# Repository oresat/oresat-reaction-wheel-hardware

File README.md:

# DO NOT TRY TO MAKE THIS

## License

This source describes Open Hardware and is licensed under the CERN-OHL-S v2.
You may redistribute and modify it under the terms of the
[CERN-OHL-S v2](https://ohwr.org/cern_ohl_s_v2.txt); the full text is in
[LICENSE](LICENSE).

This source is distributed WITHOUT ANY EXPRESS OR IMPLIED WARRANTY, INCLUDING
OF MERCHANTABILITY, SATISFACTORY QUALITY AND FITNESS FOR A PARTICULAR PURPOSE.
Please see the CERN-OHL-S v2 for applicable conditions.

Source location: https://gitlab.com/solomondg/oresat-rw-board-rev8

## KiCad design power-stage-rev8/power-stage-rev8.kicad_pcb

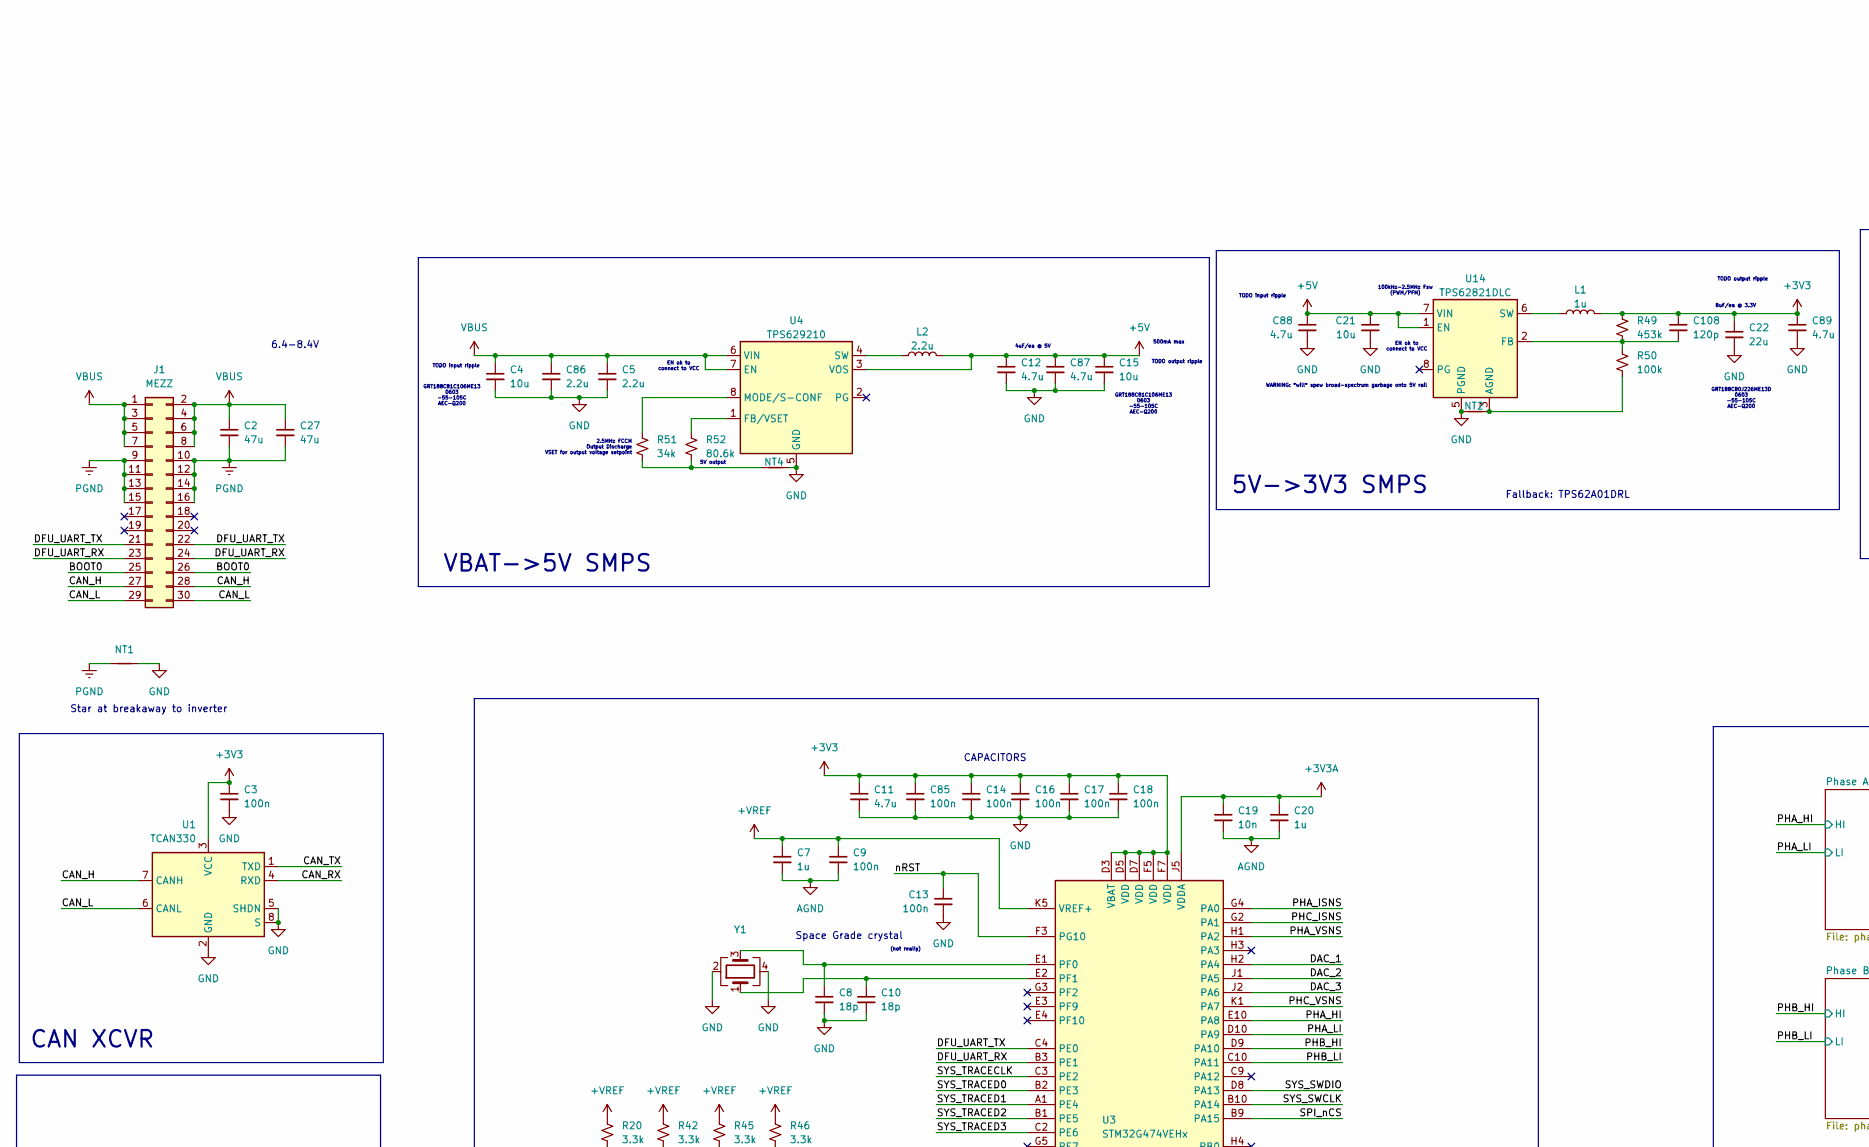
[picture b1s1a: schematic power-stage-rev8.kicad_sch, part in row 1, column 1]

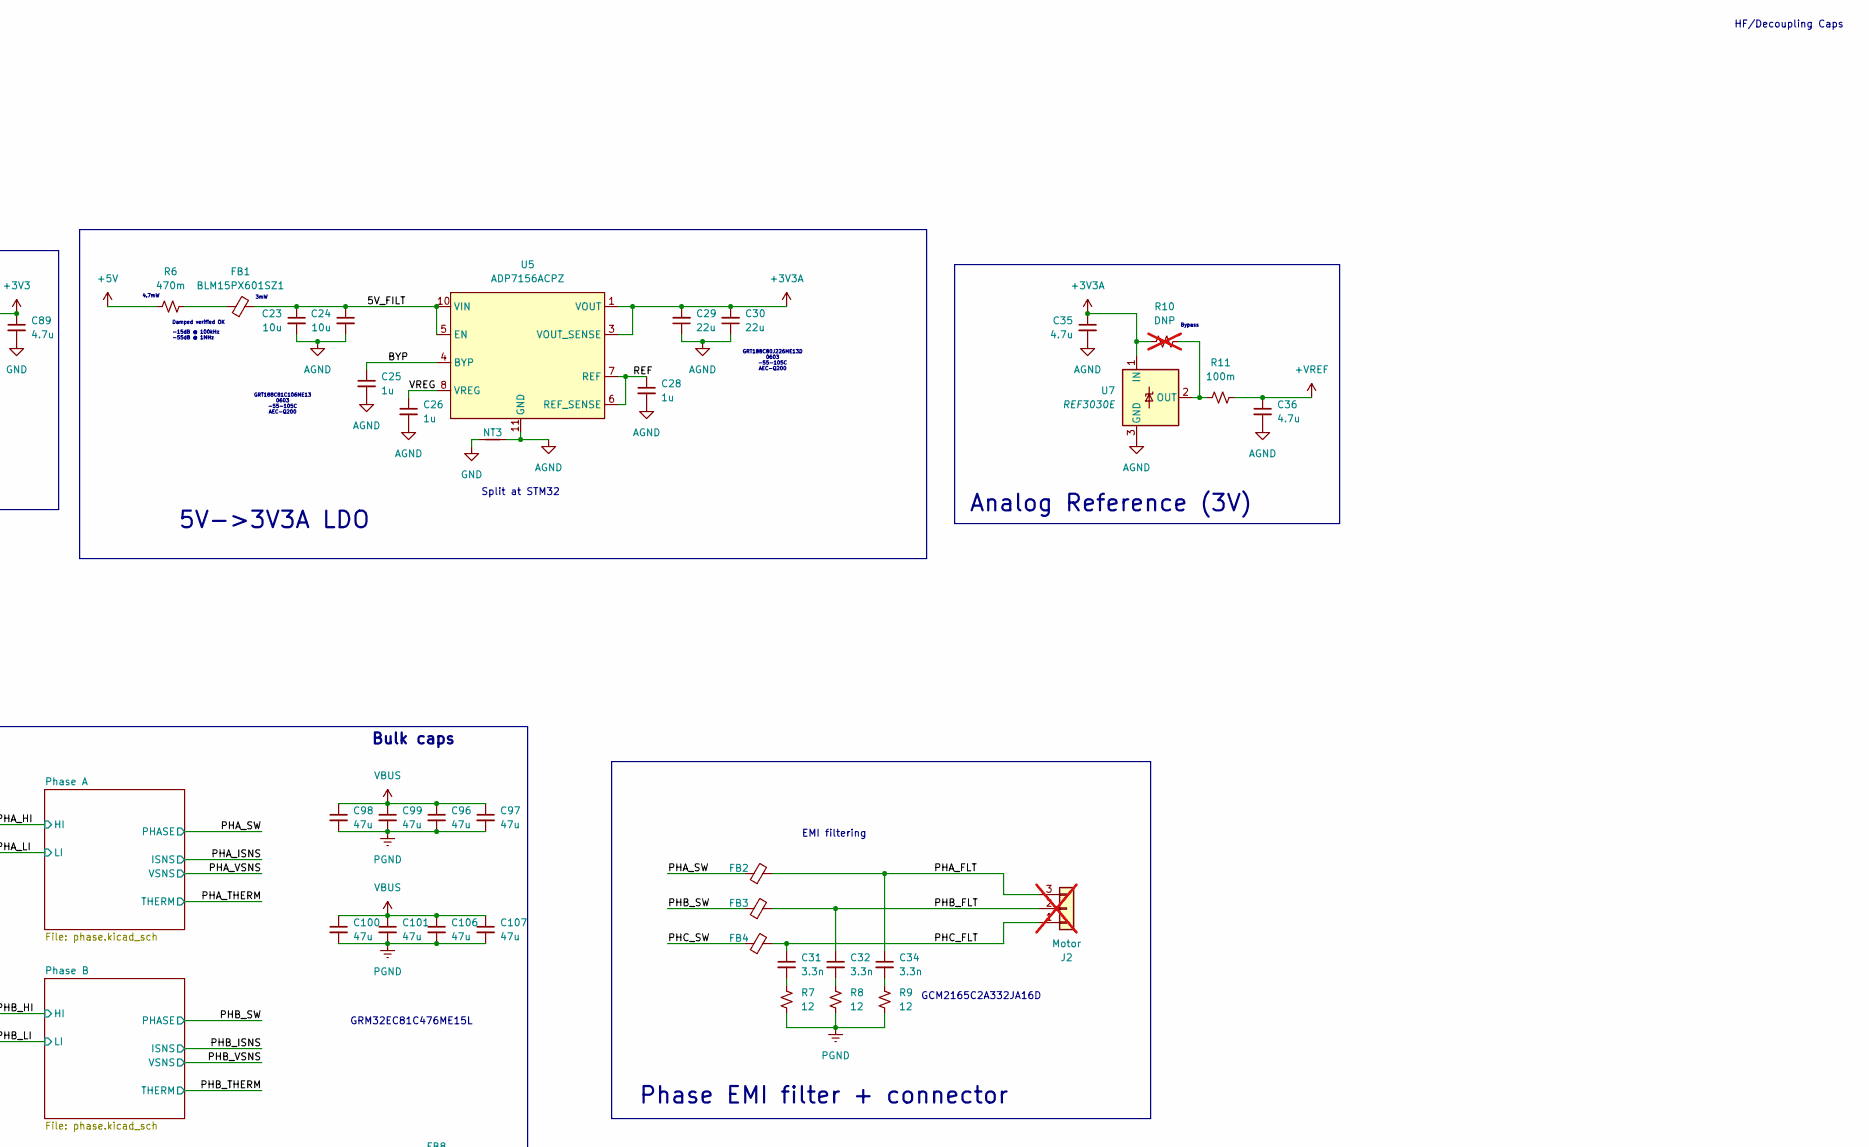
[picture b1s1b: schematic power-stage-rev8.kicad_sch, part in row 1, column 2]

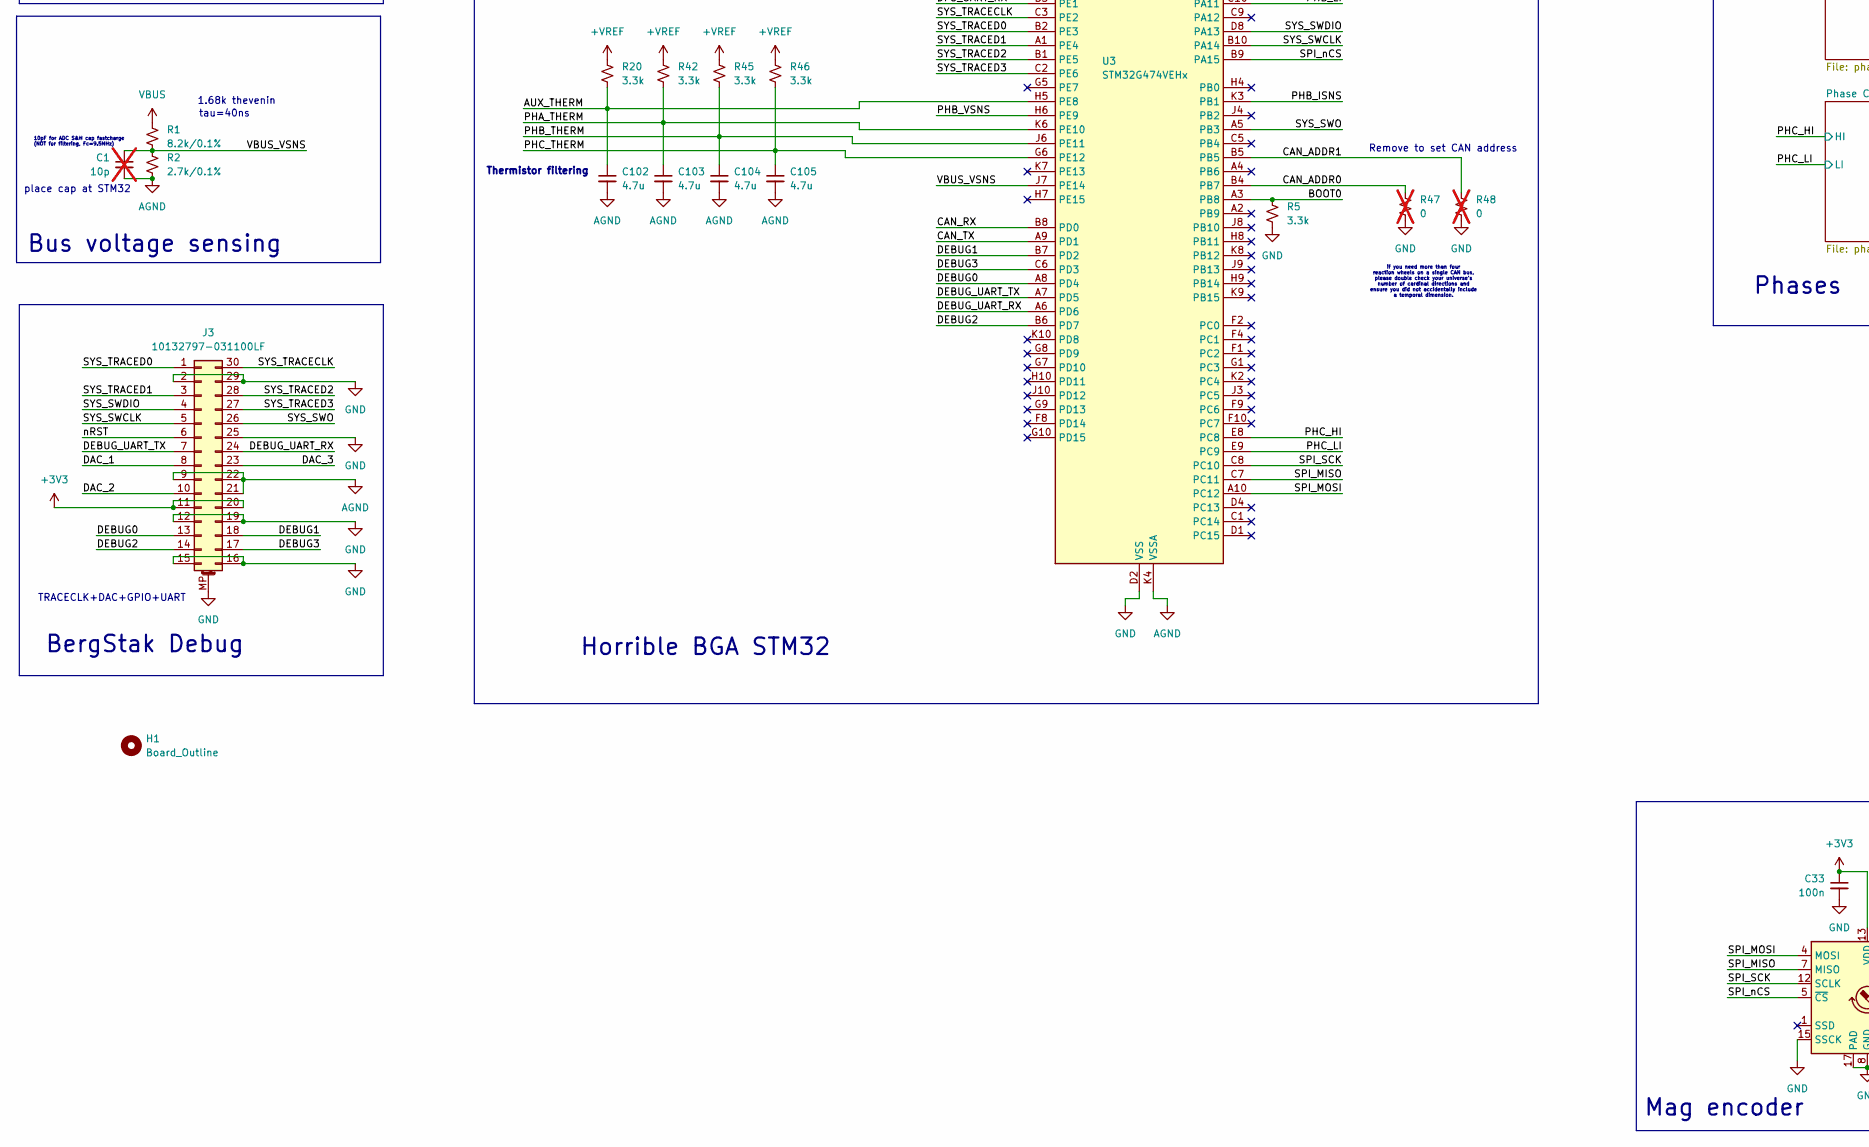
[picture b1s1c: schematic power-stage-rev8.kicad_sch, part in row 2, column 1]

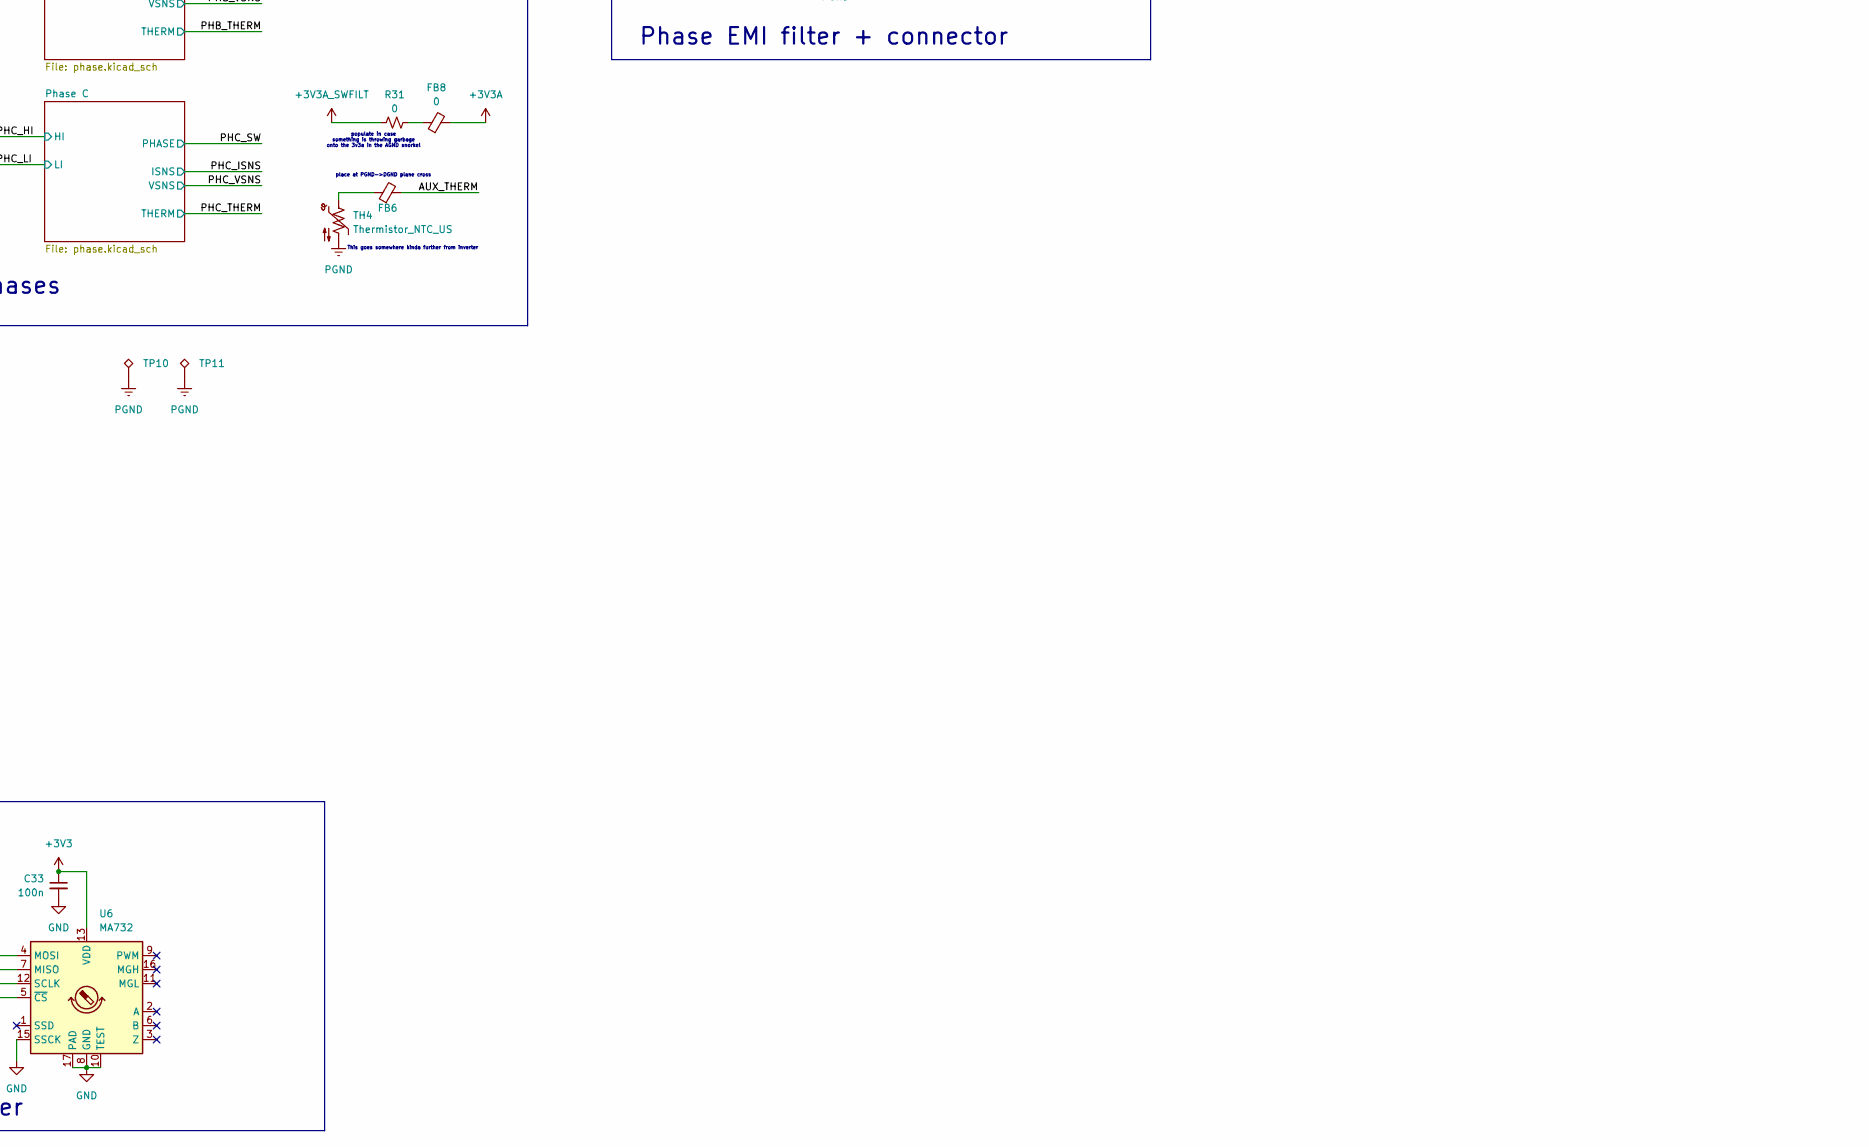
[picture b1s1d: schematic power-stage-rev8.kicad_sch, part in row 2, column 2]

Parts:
C1: 10p; C_0402_1005Metric; MPN GCM1555C1H100FA16D; not fitted
C2, C27, C96, C97, C98, C99, C100, C101, C106, C107: 47u; C_1210_3225Metric; MPN GRT32EC81C476KE13L
C3, C9, C13, C14, C16, C17, C18, C33, C85: 100n; C_0402_1005Metric; MPN GRT155R71E104KE01J
C4, C15, C21, C23, C24: 10u; C_0603_1608Metric; MPN GRT188C81C106ME13D
C5, C86: 2.2u; C_0402_1005Metric; MPN GRT155C81C225ME13D
C7, C20, C25, C26, C28: 1u; C_0402_1005Metric; MPN GRT155C81A105ME01D
C8, C10: 18p; C_0402_1005Metric; MPN GCM1555C1H180JA16D
C11, C12, C35, C36, C87, C88, C89, C102, C103, C104, C105: 4.7u; C_0402_1005Metric; MPN GRT155C81A475ME13J
C19: 10n; C_0402_1005Metric; MPN GCM155R71H103KA55D
C22, C29, C30: 22u; C_0603_1608Metric; MPN GRT188C80J226ME13D
C31, C32, C34: 3.3n; C_0805_2012Metric; MPN GCM2165C2A332JA16D
C108: 120p; C_0402_1005Metric; MPN GRM1555C1H121JA01D
FB1, FB6: BLM15PX601SZ1; L_0402_1005Metric; MPN BLM15PX601SZ1D
FB2, FB3, FB4: BLM31SN500SN1L; L_1206_3216Metric; MPN BLM31SN500SN1L
FB8: 0; L_0402_1005Metric; MPN AC0402FR-070RL
H1: Board_Outline; board_def_rev8.0
J1: MEZZ; 0555600307; MPN 0555600307
J2: Motor; Molex_Micro-Fit_3.0_43650-0315_1x03_P3.00mm_Vertical; not fitted
J3: 10132797-031100LF; 10132797-031100LF_1; MPN 10132797-031100LF
L1: 1u; L_Murata_DFE201612E_2016Metric; MPN DFE201612E-1R0M=P2
L2: 2.2u; L_Murata_DFE201612E_2016Metric; MPN DFE201612E-2R2M=P2
NT1: NetTie_2; NetTie-2_SMD_Pad2.0mm
NT2, NT3, NT4: NetTie_2; NetTie-2_SMD_Pad0.5mm
R1: 8.2k/0.1%; R_0402_1005Metric; MPN RP0402BRD078K2L
R2: 2.7k/0.1%; R_0402_1005Metric; MPN RP0402BRD072K7L
R5, R20, R42, R45, R46: 3.3k; R_0402_1005Metric; MPN AC0402FR-073K3L
R6: 470m; R_0402_1005Metric; MPN PE0402FRF7W0R47L
R7, R8, R9: 12; R_0805_2012Metric; MPN SR0805FR-7T12RL
R10: DNP; R_0402_1005Metric; not fitted
R11: 100m; R_0402_1005Metric; MPN PE0402FRF470R1L
R31: 0; R_0402_1005Metric; MPN AC0402FR-070RL
R47, R48: 0; R_0402_1005Metric; MPN AC0402FR-070RL; not fitted
R49: 453k; R_0402_1005Metric; MPN AC0402FR-07453KL
R50: 100k; R_0402_1005Metric; MPN AC0402FR-07100KL
R51: 34k; R_0402_1005Metric; MPN AC0402FR-0734KL
R52: 80.6k; R_0402_1005Metric; MPN AC0402FR-0780K6L
TH4: Thermistor_NTC_US; R_0402_1005Metric; MPN NCU15XH103F6SRC
TP10, TP11: TestPoint_Alt; TestPoint_Pad_1.0x1.0mm_NoSilk
U1: TCAN330; SOT-23-8; MPN TCAN330DCNR
U3: STM32G474VEHx; TFBGA-100_8x8mm_Layout10x10_P0.8mm; MPN STM32G474VEH3
U4: TPS629210; SOT-583-8; MPN TPS629210DRLR
U5: ADP7156ACPZ; DFN-10-1EP_3x3mm_P0.5mm_EP1.65x2.38mm; MPN ADP7156ACPZ-3.3-R7
U6: MA732; QFN-16-1EP_3x3mm_P0.5mm_EP1.75x1.75mm; MPN MA732GQ-Z
U7: REF3030E; SOT-23; MPN REF3030AIDBZR
U14: TPS62821DLC; Texas_VSON-HR-8_1.5x2mm_P0.5mm; MPN TPS62821DLCR
Y1: Crystal_GND24; Crystal_SMD_2016-4Pin_2.0x1.6mm; MPN LFXTAL071255

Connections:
+3V3: C3.1, C11.1, C14.1, C16.1, C17.1, C18.1, C22.1, C33.1, C85.1, C89.1, C108.1, J3.11, J3.20, L1.2, R49.1, U1.3 (VCC), U3.D3 (VBAT), U3.D5 (VDD), U3.D7 (VDD), U3.F5 (VDD), U3.F7 (VDD), U6.13 (VDD)
+3V3A: C19.1, C20.1, C29.2, C30.2, C35.1, FB8.2, R10.1, U3.J5 (VDDA), U5.1 (VOUT), U5.2 (VOUT), U5.3 (VOUT_SENSE), U7.1 (IN)
+3V3A_SWFILT: R31.1; also elsewhere on the board
+5V: C12.1, C15.1, C21.1, C87.1, C88.1, L2.2, R6.1, U4.3 (VOS), U14.1 (EN), U14.7 (VIN); also elsewhere on the board
+VREF: C7.1, C9.1, C36.1, R11.2, R20.1, R42.1, R45.1, R46.1, U3.K5 (VREF+); also elsewhere on the board
/5V_FILT: C23.1, C24.1, FB1.2, U5.5 (EN), U5.9 (VIN), U5.10 (VIN)
/AUX_THERM: C102.1, FB6.2, R20.2, U3.H5 (PE8)
/BOOT0: J1.25, J1.26, R5.1, U3.A3 (PB8)
/BYP: C25.1, U5.4 (BYP)
/CAN_ADDR0: R47.1, U3.B4 (PB7)
/CAN_ADDR1: R48.1, U3.B5
/CAN_H: J1.27, J1.28, U1.7 (CANH)
/CAN_L: J1.29, J1.30, U1.6 (CANL)
/CAN_RX: U1.4 (RXD), U3.B8 (PD0)
/CAN_TX: U1.1 (TXD), U3.A9 (PD1)
/DAC_1: J3.8, U3.H2 (PA4)
/DAC_2: J3.10, U3.J1 (PA5)
/DAC_3: J3.23, U3.J2 (PA6)
/DEBUG0: J3.13, U3.A8 (PD4)
/DEBUG1: J3.18, U3.B7 (PD2)
/DEBUG2: J3.14, U3.B6 (PD7)
/DEBUG3: J3.17, U3.C6 (PD3)
/DEBUG_UART_RX: J3.24, U3.A6 (PD6)
/DEBUG_UART_TX: J3.7, U3.A7 (PD5)
/DFU_UART_RX: J1.23, J1.24, U3.B3 (PE1)
/DFU_UART_TX: J1.21, J1.22, U3.C4 (PE0)
/PHA_FLT: C34.1, FB2.2, J2.3
/PHA_HI: U3.E10 (PA8); also elsewhere on the board
/PHA_ISNS: U3.G4 (PA0); also elsewhere on the board
/PHA_LI: U3.D10 (PA9); also elsewhere on the board
/PHA_SW: FB2.1; also elsewhere on the board
/PHA_THERM: C103.1, R42.2, U3.K6 (PE10); also elsewhere on the board
/PHA_VSNS: U3.H1 (PA2); also elsewhere on the board
/PHB_FLT: C32.1, FB3.2, J2.2
/PHB_HI: U3.D9 (PA10); also elsewhere on the board
/PHB_ISNS: U3.K3 (PB1); also elsewhere on the board
/PHB_LI: U3.C10 (PA11); also elsewhere on the board
/PHB_SW: FB3.1; also elsewhere on the board
/PHB_THERM: C104.1, R45.2, U3.J6 (PE11); also elsewhere on the board
/PHB_VSNS: U3.H6 (PE9); also elsewhere on the board
/PHC_FLT: C31.1, FB4.2, J2.1
/PHC_HI: U3.E8 (PC8); also elsewhere on the board
/PHC_ISNS: U3.G2 (PA1); also elsewhere on the board
/PHC_LI: U3.E9 (PC9); also elsewhere on the board
/PHC_SW: FB4.1; also elsewhere on the board
/PHC_THERM: C105.1, R46.2, U3.G6 (PE12); also elsewhere on the board
/PHC_VSNS: U3.K1 (PA7); also elsewhere on the board
/REF: C28.1, U5.6 (REF_SENSE), U5.7 (REF)
/SPI_MISO: U3.C7 (PC11), U6.7 (MISO)
/SPI_MOSI: U3.A10 (PC12), U6.4 (MOSI)
/SPI_SCK: U3.C8 (PC10), U6.12 (SCLK)
/SPI_nCS: U3.B9 (PA15), U6.5 (~CS)
/SYS_SWCLK: J3.5, U3.B10 (PA14)
/SYS_SWDIO: J3.4, U3.D8 (PA13)
/SYS_SWO: J3.26, U3.A5 (PB3)
/SYS_TRACECLK: J3.30, U3.C3 (PE2)
/SYS_TRACED0: J3.1, U3.B2 (PE3)
/SYS_TRACED1: J3.3, U3.A1 (PE4)
/SYS_TRACED2: J3.28, U3.B1 (PE5)
/SYS_TRACED3: J3.27, U3.C2 (PE6)
/VBUS_VSNS: C1.1, R1.2, R2.1, U3.J7 (PE14)
/VREG: C26.1, U5.8 (VREG)
/nRST: C13.1, J3.6, U3.F3 (PG10)
AGND: C1.2, C7.2, C9.2, C19.2, C20.2, C23.2, C24.2, C25.2, C26.2, C28.2, C29.1, C30.1, C35.2, C36.2, C102.2, C103.2, C104.2, C105.2, J3.9, J3.21, J3.22, NT3.2, R2.2, U3.K4 (VSSA), U5.11 (GND), U7.3 (GND); also elsewhere on the board
GND: C3.2, C4.2, C5.2, C8.2, C10.2, C11.2, C12.2, C13.2, C14.2, C15.2, C16.2, C17.2, C18.2, C21.2, C22.2, C33.2, C85.2, C86.2, C87.2, C88.2, C89.2, J3.2, J3.12, J3.15, J3.16, J3.19, J3.25, J3.29, J3.MP (MountPin), NT1.2, NT2.1, NT3.1, NT4.2, R5.2, R47.2, R48.2, U1.2 (GND), U1.5 (SHDN), U1.8 (S), U3.D2 (VSS), U3.D6 (VSS), U3.E5 (VSS), U3.E6 (VSS), U3.E7 (VSS), U3.F6 (VSS), U4.5 (GND), U6.8 (GND), U6.10 (TEST), U6.15 (SSCK), U6.17 (PAD), U14.5 (PGND), Y1.2, Y1.4; also elsewhere on the board
unnamed: C31.2, R7.1
unnamed: C32.2, R8.1
unnamed: C34.2, R9.1
unnamed: FB1.1, R6.2
unnamed: FB6.1, TH4.1
unnamed: FB8.1, R31.2
unnamed: NT4.1, R51.2, R52.2
unnamed: C8.1, U3.E1 (PF0), Y1.3
unnamed: C10.1, U3.E2 (PF1), Y1.1
unnamed: R52.1, U4.1 (FB/VSET)
unnamed: R51.1, U4.8 (MODE/S-CONF)
unnamed: L2.1, U4.4 (SW)
unnamed: R10.2, R11.1, U7.2 (OUT)
unnamed: NT2.2, R50.2, U14.3 (AGND)
unnamed: C108.2, R49.2, R50.1, U14.2 (FB)
unnamed: L1.1, U14.6 (SW)
PGND: C2.2, C27.2, C96.2, C97.2, C98.2, C99.2, C100.2, C101.2, C106.2, C107.2, J1.9, J1.10, J1.11, J1.12, J1.13, J1.14, J1.15, J1.16, NT1.1, R7.2, R8.2, R9.2, TH4.2, TP10.1 (1_1), TP11.1 (1_1); also elsewhere on the board
VBUS: C2.1, C4.1, C5.1, C27.1, C86.1, C96.1, C97.1, C98.1, C99.1, C100.1, C101.1, C106.1, C107.1, J1.1, J1.2, J1.3, J1.4, J1.5, J1.6, J1.7, J1.8, R1.1, U4.6 (VIN), U4.7 (EN); also elsewhere on the board

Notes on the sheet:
Horrible BGA STM32
4.7mW
8uF/ea @ 3.3V
TRACECLK+DAC+GPIO+UART
GRT188C81C106ME13 0603 -55-105C AEC-Q200
Bypass
-15dB @ 100kHz -55dB @ 1MHz
populate in case something is throwing garbage onto the 3v3a in the AGND snorkel
Space Grade crystal
place at PGND->DGND plane cross
3mW
Bulk caps
GRT188C80J226ME13D 0603 -55-105C AEC-Q200
tau=40ns
VBAT->5V SMPS
2.5MHz FCCM Output Discharge VSET for output voltage setpoint
500mA max
(not really)
10pF for ADC S&H cap fastcharge (NOT for filtering, Fc=9.5MHz)
CAN XCVR
EN ok to connect to VCC
CAPACITORS
TODO output ripple
Remove to set CAN address
Bus voltage sensing
TODO input ripple
This goes somewhere kinda further from inverter
HF/Decoupling Caps
Mag encoder
1.68k thevenin
Star at breakaway to inverter
EMI filtering
if you need more than four reaction wheels on a single CAN bus, please double check your universe's number of cardinal directions and ensure you did not accidentally include a temporal dimension.
place cap at STM32
Split at STM32
100kHz-2.5MHz Fsw (PWM/PFM)
GRM32EC81C476ME15L
Damped verified OK
4uF/ea @ 5V
Phases

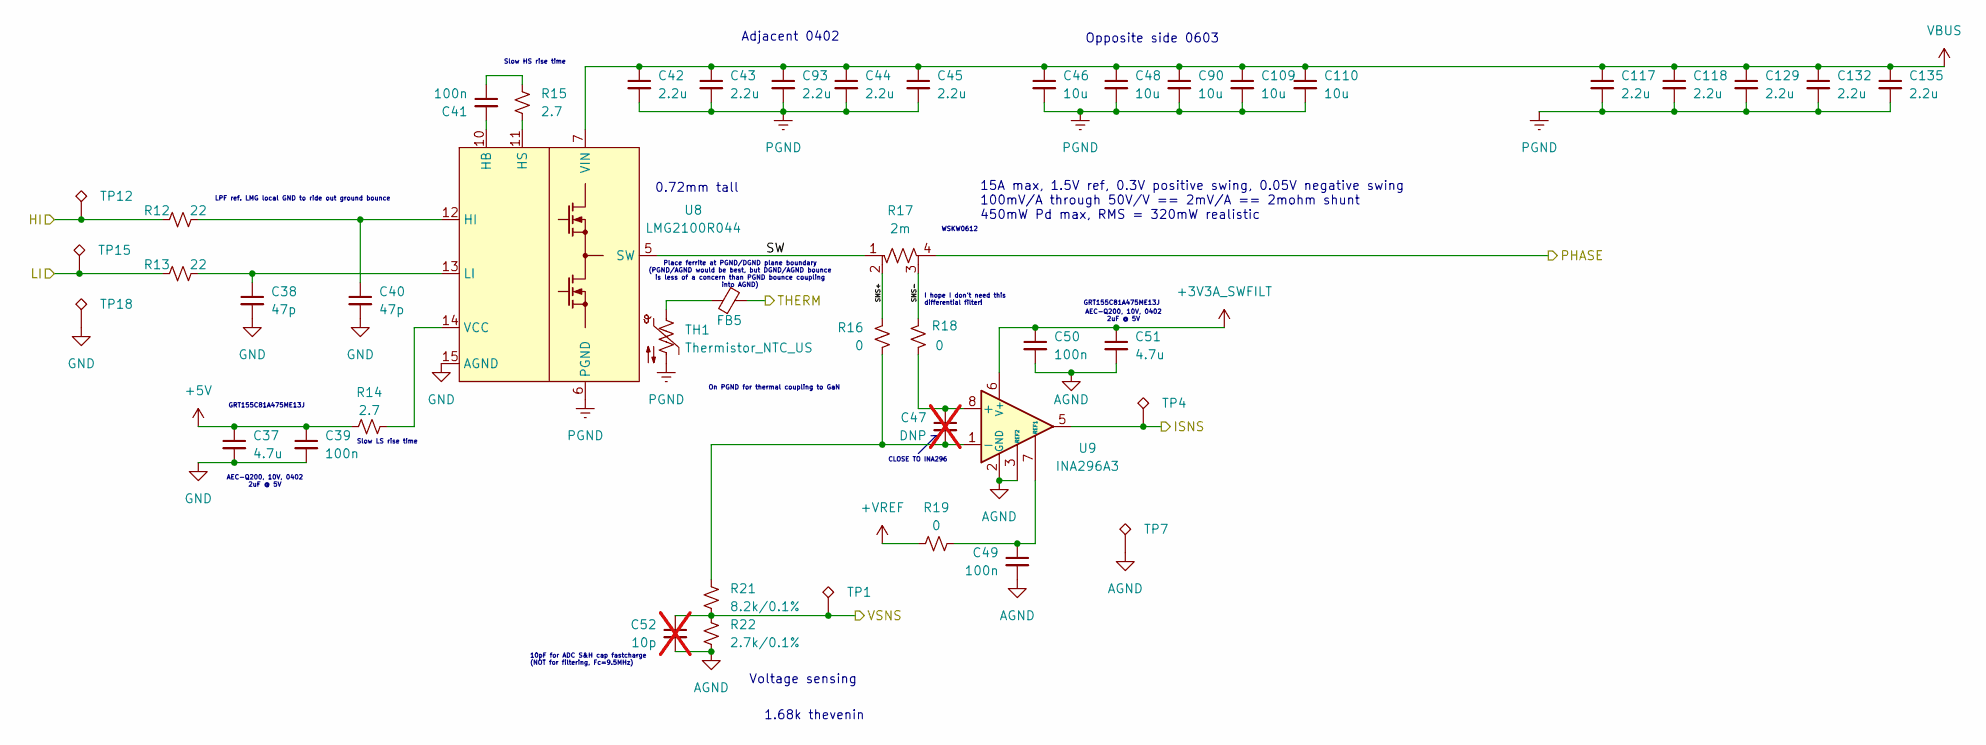
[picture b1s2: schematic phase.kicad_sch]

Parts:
C37, C51: 4.7u; C_0402_1005Metric; MPN GRT155C81A475ME13J
C38, C40: 47p; C_0402_1005Metric; MPN GCM1555C1H470JA16D
C39, C41, C49, C50: 100n; C_0402_1005Metric; MPN GRT155R71E104KE01J
C42, C43, C44, C45, C93, C117, C118, C129, C132, C135: 2.2u; C_0402_1005Metric; MPN GRT155C81C225ME13D
C46, C48, C90, C109, C110: 10u; C_0603_1608Metric; MPN GRT188C81C106ME13D
C47: DNP; C_0402_1005Metric; not fitted
C52: 10p; C_0402_1005Metric; MPN GCM1555C1H100FA16D; not fitted
FB5: BLM15PX601SZ1; L_0402_1005Metric; MPN BLM15PX601SZ1D
R12, R13: 22; R_0402_1005Metric; MPN AC0402FR-0722RL
R14, R15: 2.7; R_0402_1005Metric; MPN AC0402FR-072R7L
R16, R18, R19: 0; R_0402_1005Metric; MPN AC0402FR-070RL
R17: 2m; R_Shunt_Vishay_WSKW0612; MPN WSKW06122L000FEA
R21: 8.2k/0.1%; R_0402_1005Metric; MPN RP0402BRD078K2L
R22: 2.7k/0.1%; R_0402_1005Metric; MPN RP0402BRD072K7L
TH1: Thermistor_NTC_US; R_0402_1005Metric; MPN NCU15XH103F6SRC
TP1, TP4, TP7, TP12, TP15, TP18: TestPoint_Alt; TestPoint_Pad_1.0x1.0mm_NoSilk
U8: LMG2100R044; TI_torment_nexus; MPN LMG2100R044RARR
U9: INA296A3; SOT-23-8; MPN INA296A3QDDFRQ1

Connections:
+3V3A_SWFILT: C50.1, C51.1, U9.6 (V+); also elsewhere on the board
+5V: C37.1, C39.1, R14.1; also elsewhere on the board
+VREF: R19.1; also elsewhere on the board
/PHA_HI: R12.2, TP12.1 (1_1); also elsewhere on the board
/PHA_ISNS: TP4.1 (1_1), U9.5; also elsewhere on the board
/PHA_LI: R13.1, TP15.1 (1_1); also elsewhere on the board
/PHA_SW: R17.4; also elsewhere on the board
/PHA_THERM: FB5.2; also elsewhere on the board
/PHA_VSNS: C52.1, R21.2, R22.1, TP1.1 (1_1); also elsewhere on the board
/Phase A/SNS+: R16.1, R17.2
/Phase A/SNS-: R17.3, R18.2
/Phase A/SW: R17.1, U8.5 (SW)
AGND: C49.2, C50.2, C51.2, C52.2, R22.2, TP7.1 (1_1), U9.2 (GND), U9.3 (REF2), U9.4 (GND); also elsewhere on the board
GND: C37.2, C38.2, C39.2, C40.2, TP18.1 (1_1), U8.15 (AGND); also elsewhere on the board
unnamed: C41.1, R15.1
unnamed: FB5.1, TH1.1
unnamed: C41.2, U8.10 (HB)
unnamed: C40.1, R12.1, U8.12 (HI)
unnamed: R15.2, U8.11 (HS)
unnamed: C38.1, R13.2, U8.13 (LI)
unnamed: R14.2, U8.14 (VCC)
unnamed: C47.1, R18.1, U9.8 (+)
unnamed: C47.2, R16.2, R21.1, U9.1 (-)
unnamed: C49.1, R19.2, U9.7 (REF1)
PGND: C42.2, C43.2, C44.2, C45.2, C46.2, C48.2, C90.2, C93.2, C109.2, C110.2, C117.2, C118.2, C129.2, C132.2, C135.2, TH1.2, U8.6 (PGND), U8.17 (PGND); also elsewhere on the board
VBUS: C42.1, C43.1, C44.1, C45.1, C46.1, C48.1, C90.1, C93.1, C109.1, C110.1, C117.1, C118.1, C129.1, C132.1, C135.1, U8.7 (VIN); also elsewhere on the board

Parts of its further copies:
C53, C67, C69, C83: 4.7u; C_0402_1005Metric; MPN GRT155C81A475ME13J
C54, C56, C70, C72: 47p; C_0402_1005Metric; MPN GCM1555C1H470JA16D
C55, C57, C65, C66, C71, C73, C81, C82: 100n; C_0402_1005Metric; MPN GRT155R71E104KE01J
C58, C59, C60, C61, C74, C75, C76, C77, C94, C95, C122, C123, C127, C128, C130, C131, C133, C134, C136, C137: 2.2u; C_0402_1005Metric; MPN GRT155C81C225ME13D
C62, C64, C78, C80, C91, C92, C112, C113, C115, C116: 10u; C_0603_1608Metric; MPN GRT188C81C106ME13D
C63, C79: DNP; C_0402_1005Metric; not fitted
C68, C84: 10p; C_0402_1005Metric; MPN GCM1555C1H100FA16D; not fitted
FB7, FB9: BLM15PX601SZ1; L_0402_1005Metric; MPN BLM15PX601SZ1D
R23, R24, R34, R35: 22; R_0402_1005Metric; MPN AC0402FR-0722RL
R25, R26, R36, R37: 2.7; R_0402_1005Metric; MPN AC0402FR-072R7L
R27, R29, R30, R38, R40, R41: 0; R_0402_1005Metric; MPN AC0402FR-070RL
R28, R39: 2m; R_Shunt_Vishay_WSKW0612; MPN WSKW06122L000FEA
R32, R43: 8.2k/0.1%; R_0402_1005Metric; MPN RP0402BRD078K2L
R33, R44: 2.7k/0.1%; R_0402_1005Metric; MPN RP0402BRD072K7L
TH2, TH3: Thermistor_NTC_US; R_0402_1005Metric; MPN NCU15XH103F6SRC
TP2, TP3, TP5, TP6, TP8, TP9, TP13, TP14, TP16, TP17, TP19, TP20: TestPoint_Alt; TestPoint_Pad_1.0x1.0mm_NoSilk
U10, U12: LMG2100R044; TI_torment_nexus; MPN LMG2100R044RARR
U11, U13: INA296A3; SOT-23-8; MPN INA296A3QDDFRQ1

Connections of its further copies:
+3V3A_SWFILT: C66.1, C67.1, C82.1, C83.1, U11.6 (V+), U13.6 (V+); also elsewhere on the board
+5V: C53.1, C55.1, C69.1, C71.1, R25.1, R36.1; also elsewhere on the board
+VREF: R30.1, R41.1; also elsewhere on the board
/PHB_HI: R23.2, TP13.1 (1_1); also elsewhere on the board
/PHB_ISNS: TP5.1 (1_1), U11.5; also elsewhere on the board
/PHB_LI: R24.1, TP16.1 (1_1); also elsewhere on the board
/PHB_SW: R28.4; also elsewhere on the board
/PHB_THERM: FB7.2; also elsewhere on the board
/PHB_VSNS: C68.1, R32.2, R33.1, TP2.1 (1_1); also elsewhere on the board
/PHC_HI: R34.2, TP14.1 (1_1); also elsewhere on the board
/PHC_ISNS: TP6.1 (1_1), U13.5; also elsewhere on the board
/PHC_LI: R35.1, TP17.1 (1_1); also elsewhere on the board
/PHC_SW: R39.4; also elsewhere on the board
/PHC_THERM: FB9.2; also elsewhere on the board
/PHC_VSNS: C84.1, R43.2, R44.1, TP3.1 (1_1); also elsewhere on the board
/Phase B/SNS+: R27.1, R28.2
/Phase B/SNS-: R28.3, R29.2
/Phase B/SW: R28.1, U10.5 (SW)
/Phase C/SNS+: R38.1, R39.2
/Phase C/SNS-: R39.3, R40.2
/Phase C/SW: R39.1, U12.5 (SW)
AGND: C65.2, C66.2, C67.2, C68.2, C81.2, C82.2, C83.2, C84.2, R33.2, R44.2, TP8.1 (1_1), TP9.1 (1_1), U11.2 (GND), U11.3 (REF2), U11.4 (GND), U13.2 (GND), U13.3 (REF2), U13.4 (GND); also elsewhere on the board
GND: C53.2, C54.2, C55.2, C56.2, C69.2, C70.2, C71.2, C72.2, TP19.1 (1_1), TP20.1 (1_1), U10.15 (AGND), U12.15 (AGND); also elsewhere on the board
unnamed: C57.1, R26.1
unnamed: C73.1, R37.1
unnamed: FB7.1, TH2.1
unnamed: FB9.1, TH3.1
unnamed: C57.2, U10.10 (HB)
unnamed: C56.1, R23.1, U10.12 (HI)
unnamed: R26.2, U10.11 (HS)
unnamed: C54.1, R24.2, U10.13 (LI)
unnamed: R25.2, U10.14 (VCC)
unnamed: C63.1, R29.1, U11.8 (+)
unnamed: C63.2, R27.2, R32.1, U11.1 (-)
unnamed: C65.1, R30.2, U11.7 (REF1)
unnamed: C73.2, U12.10 (HB)
unnamed: C72.1, R34.1, U12.12 (HI)
unnamed: R37.2, U12.11 (HS)
unnamed: C70.1, R35.2, U12.13 (LI)
unnamed: R36.2, U12.14 (VCC)
unnamed: C79.1, R40.1, U13.8 (+)
unnamed: C79.2, R38.2, R43.1, U13.1 (-)
unnamed: C81.1, R41.2, U13.7 (REF1)
PGND: C58.2, C59.2, C60.2, C61.2, C62.2, C64.2, C74.2, C75.2, C76.2, C77.2, C78.2, C80.2, C91.2, C92.2, C94.2, C95.2, C112.2, C113.2, C115.2, C116.2, C122.2, C123.2, C127.2, C128.2, C130.2, C131.2, C133.2, C134.2, C136.2, C137.2, TH2.2, TH3.2, U10.6 (PGND), U10.17 (PGND), U12.6 (PGND), U12.17 (PGND); also elsewhere on the board
VBUS: C58.1, C59.1, C60.1, C61.1, C62.1, C64.1, C74.1, C75.1, C76.1, C77.1, C78.1, C80.1, C91.1, C92.1, C94.1, C95.1, C112.1, C113.1, C115.1, C116.1, C122.1, C123.1, C127.1, C128.1, C130.1, C131.1, C133.1, C134.1, C136.1, C137.1, U10.7 (VIN), U12.7 (VIN); also elsewhere on the board

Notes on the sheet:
0.72mm tall
I hope I don't need this differential filter!
On PGND for thermal coupling to GaN
1.68k thevenin
Opposite side 0603
Adjacent 0402
WSKW0612
GRT155C81A475ME13J
Slow HS rise time
Voltage sensing
AEC-Q200, 10V, 0402 2uF @ 5V
Place ferrite at PGND/DGND plane boundary (PGND/AGND would be best, but DGND/AGND bounce is less of a concern than PGND bounce coupling into AGND)
10pF for ADC S&H cap fastcharge (NOT for filtering, Fc=9.5MHz)
Slow LS rise time
LPF ref. LMG local GND to ride out ground bounce
CLOSE TO INA296
15A max, 1.5V ref, 0.3V positive swing, 0.05V negative swing 100mV/A through 50V/V == 2mV/A == 2mohm shunt 450mW Pd max, RMS = 320mW realistic
